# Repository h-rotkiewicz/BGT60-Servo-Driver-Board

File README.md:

# BGT60 Servo Driver Board

A USB-C powered control board built around an STM32U5 microcontroller, featuring a FFC connector interface to a BGT60TR13C radar daughterboard for non-contact sensing, and six independent DC motor/servo outputs for actuation.

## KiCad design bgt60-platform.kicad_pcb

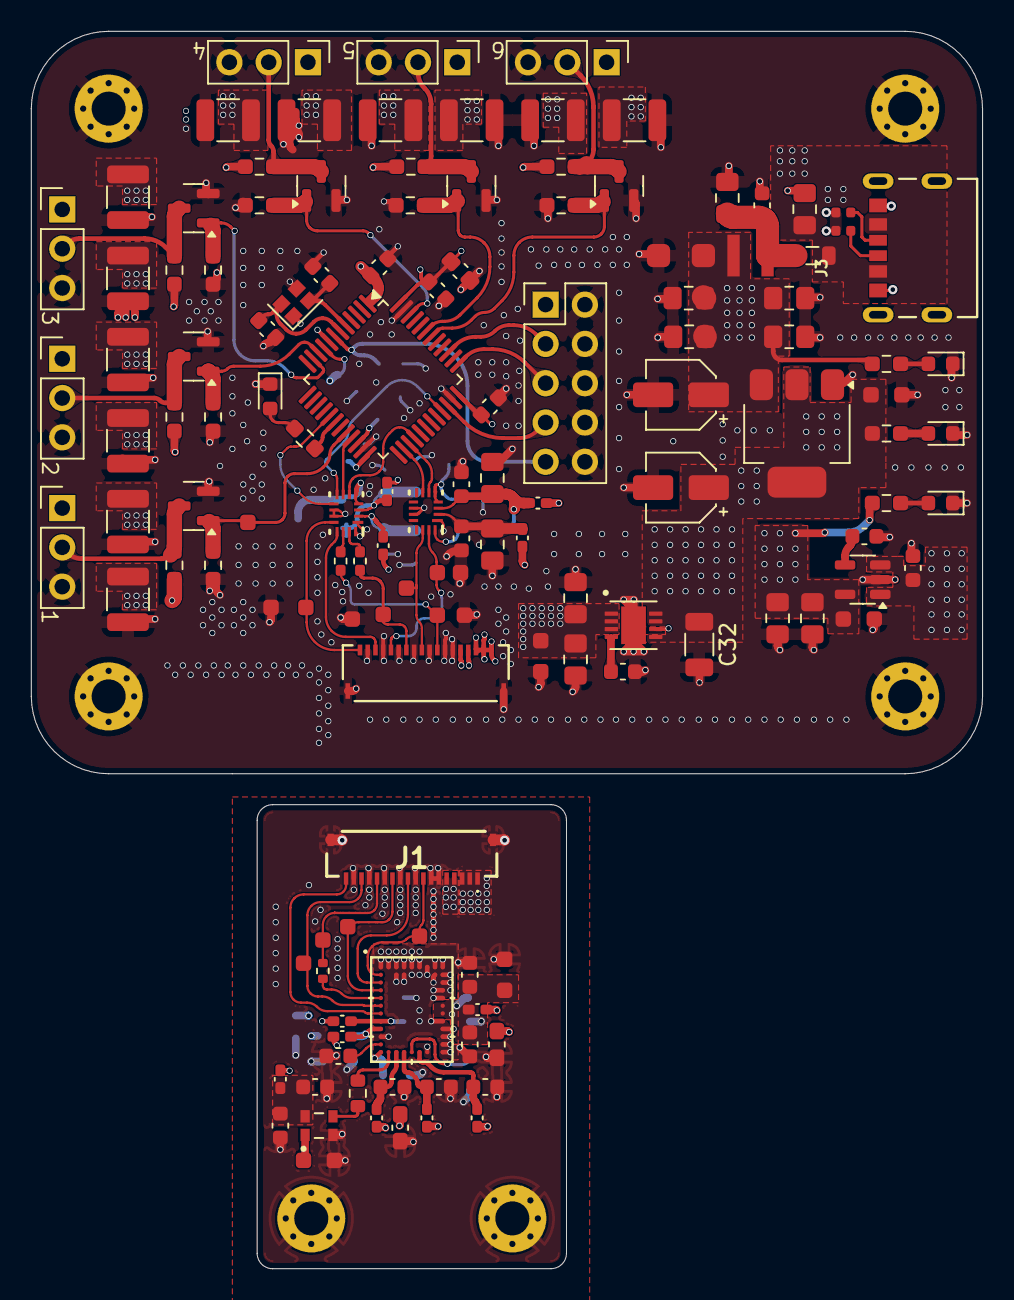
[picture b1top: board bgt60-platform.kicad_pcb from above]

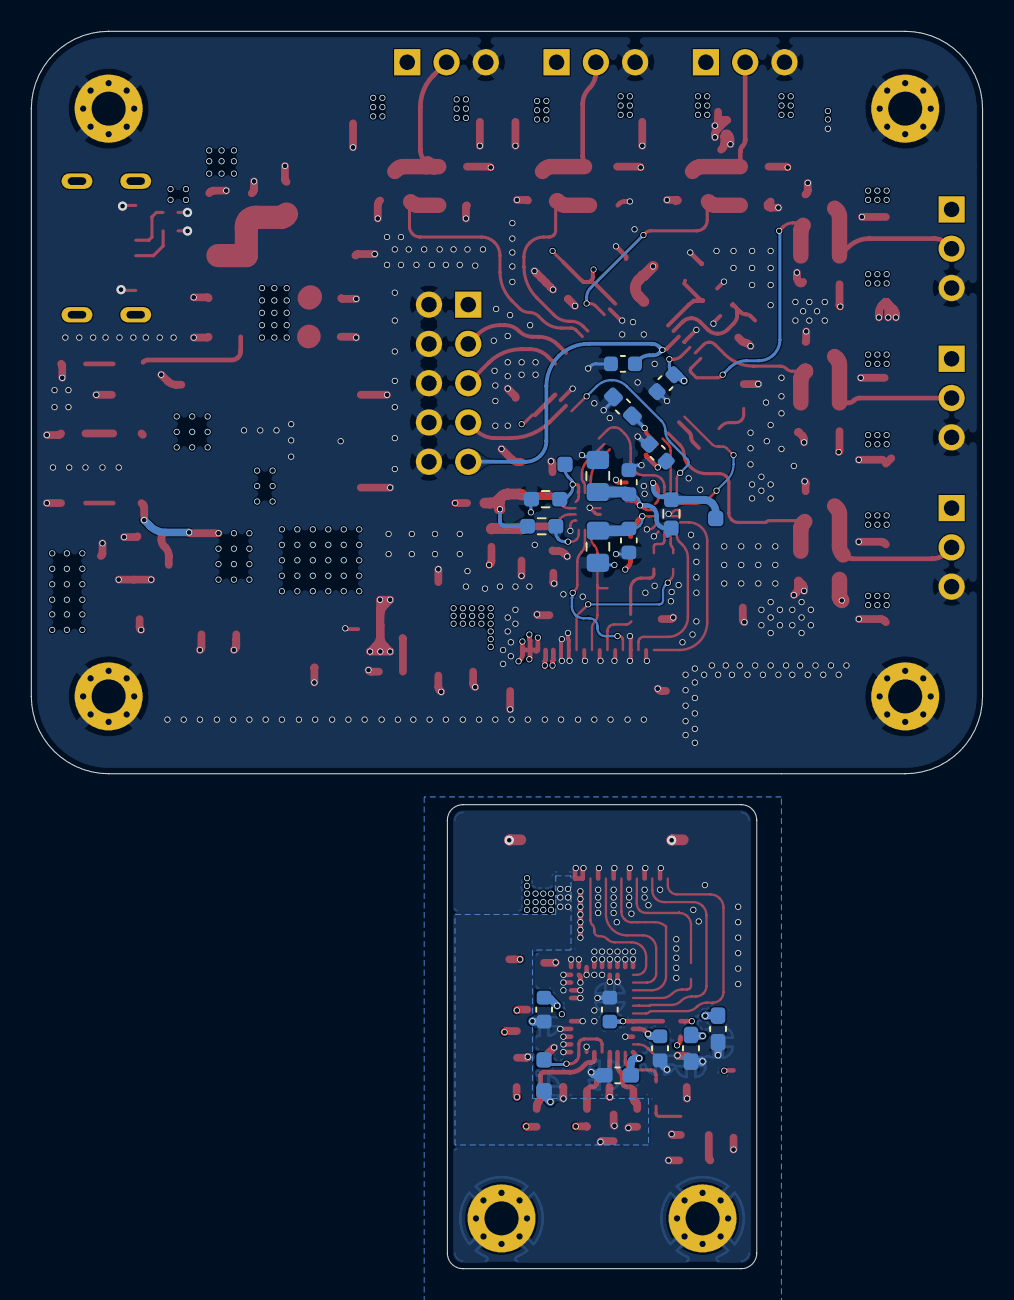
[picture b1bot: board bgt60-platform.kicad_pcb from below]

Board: 4 copper layers, 61.5 x 80.0 mm, 157 parts (20 on the bottom side), 76 nets.

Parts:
C1, C5, C7, C21, C22, C23, C24, C25, C51#2: 10u; C_0805_2012Metric_Pad1.18x1.45mm_HandSolder
C2: 100u; C_0805_2012Metric_Pad1.18x1.45mm_HandSolder
C3, C4, C6, C8, C26, C41, C42, C43, C44, C45, C46, C47, C48, C49: 1u; C_0603_1608Metric
C9, C16: 4.7u; C_0603_1608Metric_Pad1.08x0.95mm_HandSolder
C10, C14: 4p; C_0603_1608Metric
C11, C12, C13, C15, C17, C18, C20, C50: 100n; C_0603_1608Metric
C27, C29: 10u; CP_Elec_4x3
C28: 0.47n; C_0603_1608Metric
C30, C31, C34, C35: 22u; C_0805_2012Metric_Pad1.18x1.45mm_HandSolder
C32: 10u; C_1206_3216Metric
C33: 1n; C_0603_1608Metric
C36, C37, C38, C39, C40: 10u; C_0603_1608Metric_Pad1.08x0.95mm_HandSolder
C51: 470n; C_0603_1608Metric
C52, C53, C54, C55, C56, C57, C58, C59, C60, C61, C62, C63: 47u; C_1210_3225Metric
D1: LED YG; LED_0603_1608Metric
D2, D3, D4: LED GREEN; D_0603_1608Metric
FB1, FB2, FB3, FB4, FB6, FB7, FB8, FB9, FB10, FB11, FB12: 600@100M; L_0402_1005Metric_Pad0.77x0.64mm_HandSolder
FB5: 120@100M; L_0805_2012Metric
H1, H2, H3, H4: MountingHole_Pad; MountingHole_2.2mm_M2_Pad_Via
J1: 0.5K-HX-18PWB; 05KHX18PWB
J1#2: 5034801800; CON_5034801800_MOL
J2: SWD; PinHeader_2x05_P2.54mm_Vertical
J3: USB-C_CUI_UJC-HP-3-SMT-TR; USB-C_Receptacle_CUI_UJC-HP-3-SMT-TR
L1: 10u; L_1212
Q1, Q2, Q3, Q4, Q5, Q6: 2N7002BK; SOT-23
R1, R2, R3, R10, R11, R12, R16, R17, R18: 5k; R_0603_1608Metric_Pad0.98x0.95mm_HandSolder
R4, R7, R8, R9: 1k; R_0603_1608Metric_Pad0.98x0.95mm_HandSolder
R5, R6: R_5k1_0402; R_0402_1005Metric
R13, R14, R15, R19, R20, R21: 10k; R_0603_1608Metric_Pad0.98x0.95mm_HandSolder
R22: 150R; R_0603_1608Metric
R27, R28: 22; R_0402_1005Metric_Pad0.72x0.64mm_HandSolder
R29: 22; R_0402_1005Metric
Servo_1, Servo_2, Servo_3, Servo_4, Servo_5, Servo_6: Conn_01x03; PinHeader_1x03_P2.54mm_Vertical
TP1, TP1#2, TP2, TP2#2, TP3, TP3#2, TP4, TP4#2, TP5, TP6, TP7, TP8, TP9, TP14, TP17#2, TP18: TestPoint
TP10, TP11, TP12, TP13, TP15, TP16, TP17: TestPoint; Test pads 2 terminal
U1, U2: SN74AVCH4T245RSVR; RSV0016A
U3: STM32U585CIT3; LQFP-48_7x7mm_P0.5mm
U4: LD1117S33TR; SOT-223-3_TabPin2
U5: MIC5207-3.3YM5-TR; SOT-23-5
U6: ADM7170ACPZ-1.8-R7; SON50P300X300X80-9N
U7: BGT60TR13CE6327XUMA1; PG-VF2BGA-40-1
Y1: Crystal_GND23_Small; Crystal_SMD_2016-4Pin_2.0x1.6mm
Y2: KC2016Z80.0000C15XXK; OSC_KC2016Z80.0000C15XXK-4

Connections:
1.8VDR: C36.1, C38.1, C39.1, FB6.1, FB8.1, FB9.1, FB10.1, FB11.1, FB12.2, J1.1, J1.2, J1.3
1.8VDR_BB: C34.1, C35.1, FB1.1, FB3.1, J1#2.16, J1#2.17, J1#2.18, TP13.1, U6.1 (VOUT), U6.2 (VOUT__1), U6.3 (SENSE)
5V: C22.1, C23.1, C24.1, C25.1, C26.1, C27.1, L1.2, R7.1, R10.2, R11.2, R12.2, R16.2, R17.2, R18.2, TP10.1, U4.3 (VI), U5.1 (IN), U5.3 (EN)
+3V3: C9.1, C11.1, C13.1, C15.1, C17.1, C18.1, C29.1, C32.1, FB2.1, FB4.2, J2.1, R8.1, TP12.1, U3.1 (VBAT), U3.9 (VDDA), U3.24 (VDD), U3.36 (VDD), U3.48 (VDD), U4.2 (VO), U6.5 (EN), U6.7 (VIN), U6.8 (VIN__1)
+3V3R: C37.1, FB7.1, J1.4, J1.5
+3V3R_BB: C30.1, C31.1, J1#2.14, J1#2.15, R9.1, TP11.1, U5.5 (OUT)
/BGT_IRQ: J1.10, U1.7 (1A2), U3.26 (PB13), U7.C1 (IRQ)
/BGT_IRQ1.8V: J1#2.9, TP5.1 (1_1), U1.14 (1B2)
/BGT_RST: J1.16, TP4.1, U7.F1 (DIO3)
/BGT_RST1.8V: J1#2.3, U2.13 (2B1)
/BGT_reset: U2.8 (2A1), U3.33 (PA12)
/NRST: C12.1, J2.9, U3.7 (NRST)
/OSC_80M: R22.2, U7.M2 (OSC_CLK)
/PH0: C10.1, U3.5 (PH0), Y1.2
/PH1: C14.1, U3.6 (PH1), Y1.4
/PWM1: Q1.3 (D), R10.1, Servo_1.2
/PWM2: Q2.3 (D), R11.1, Servo_2.2
/PWM3: Q3.3 (D), R12.1, Servo_3.2
/PWM4: Q4.3 (D), R16.1, Servo_4.2
/PWM5: Q5.3 (D), R17.1, Servo_5.2
/PWM6: Q6.3 (D), R18.1, Servo_6.2
/PWM_GEN1: Q1.1 (G), R13.2, TP14.1 (1_1), U3.20 (PB2)
/PWM_GEN2: Q2.1 (G), R14.2, U3.46 (PB9)
/PWM_GEN3: Q3.1 (G), R15.2, U3.43 (PB7)
/PWM_GEN4: Q4.1 (G), R19.2, U3.42 (PB6)
/PWM_GEN5: Q5.1 (G), R20.2, U3.10 (PA0)
/PWM_GEN6: Q6.1 (G), R21.2, U3.11 (PA1)
/SPI2_MISO: U1.6 (1A1), U3.27 (PB14)
/SPI2_MOSI: U2.6 (1A1), U3.28 (PB15)
/SPI2_NSS: U2.9 (2A2), U3.17 (PA7)
/SPI2_SCK: U2.7 (1A2), U3.21 (PB10)
/SPI_CLK: J1.8, TP3.1, U7.B1 (CLK)
/SPI_CLK1.8V: J1#2.11, R28.1, TP2#2.1 (1_1)
/SPI_MISO: J1.14, R29.1, TP1.1
/SPI_MISO1.8V: J1#2.5, TP4#2.1 (1_1), U1.15 (1B1)
/SPI_MOSI: J1.12, TP2.1, U7.D1 (DI)
/SPI_MOSI1.8V: J1#2.7, R27.1, TP3#2.1 (1_1)
/SWCLK: J2.5, U3.37 (PA14)
/SWDIO: J2.7, U3.34 (PA13)
/SWO: J2.3, U3.39 (PB3)
/VCCA: C1.1, C3.1, FB2.2, R3.1, U2.3 (VCCA)
/VCCB: C2.1, C4.1, FB1.2, U2.2 (VCCB)
/VDDA: C43.1, FB9.2, U7.J1 (VDDA)
/VDDD: C42.1, FB8.2, U7.H1 (VDDD)
/VDDLF: C41.1, FB7.2, U7.M3 (VDDLF)
/VDDPLL: C47.1, FB10.2, U7.M4 (VDDPLL)
/VDDRF: C40.1, C44.1, C45.1, C46.1, FB6.2, TP17.1, U7.F9 (VDDRF), U7.G9 (VDDRF), U7.M1 (VDDRF)
/VDDVCO: C48.1, FB11.2, U7.M6 (VDDVCO)
/~SPI_CS: J1.18, U7.G1 (CS_N)
/~SPI_CS1.8V: J1#2.1, TP1#2.1 (1_1), U2.12 (2B2)
GND: C1.2, C2.2, C3.2, C4.2, C5.2, C6.2, C7.2, C8.2, C9.2, C10.2, C11.2, C12.2, C13.2, C14.2, C15.2, C16.2, C17.2, C18.2, C20.2, C21.2, C22.2, C23.2, C24.2, C25.2, C26.2, C27.2, C28.2, C29.2, C30.2, C31.2, C32.2, C33.2, C34.2, C35.2, C36.2, C37.2, C38.2, C39.2, C40.2, C41.2, C42.2, C43.2, C44.2, C45.2, C46.2, C47.2, C48.2, C49.2, C50.2, C51.2, C51#2.2, C52.2, C53.2, C54.2, C55.2, C56.2, C57.2, C58.2, C59.2, C60.2, C61.2, C62.2, C63.2, D1.1 (K), D2.1 (K), D3.1 (K), D4.1 (K), H1.1 (1_1), H2.1 (1_1), H3.1 (1_1), H4.1 (1_1), J1.6, J1.7, J1.9, J1.11, J1.13, J1.15, J1.17, J1.MP1, J1.MP2, J1#2.2, J1#2.4, J1#2.6, J1#2.8, J1#2.10, J1#2.12, J1#2.13, J1#2.P1, J1#2.P2, J2.2, J2.4, J2.6, J2.8, J2.10, J3.A12 (GND), J3.B12 (GND), Q1.2 (S), Q2.2 (S), Q3.2 (S), Q4.2 (S), Q5.2 (S), Q6.2 (S), R2.2, R5.1, R6.1, R13.1, R14.1, R15.1, R19.1, R20.1, R21.1, Servo_1.3, Servo_2.3, Servo_3.3, Servo_4.3, Servo_5.3, Servo_6.3, TP6.1 (1_1), TP7.1 (1_1), TP10.2, TP11.2, TP12.2, TP13.2, TP15.2, TP16.2, TP17.2, TP17#2.1 (1_1), TP18.1 (1_1), U1.1 (1OE_N), U1.10 (GND), U1.11 (GND), U2.1 (1OE_N), U2.10 (GND), U2.11 (GND), U2.16 (2OE_N), U3.8 (VSSA), U3.23 (VSS), U3.35 (VSS), U3.47 (VSS), U4.1 (GND), U5.2 (GND), U6.6 (GND), U6.9 (EXP), U7.A1 (VSSD), U7.A2 (VSSD), U7.A3 (VSSRF), U7.A4 (VSSRF), U7.A5 (VSSRF), U7.A6 (VSSRF), U7.A7 (VSSRF), U7.A8 (VSSRF), U7.A9 (VSSRF), U7.B3 (VSSRF), U7.B4 (VSSRF), U7.B8 (VSSRF), U7.B9 (VSSRF), U7.C9 (VSSRF), U7.D9 (VSSRF), U7.E9 (VSSRF), U7.H9 (VSSRF), U7.J9 (VSSRF), U7.K1 (VSSA), U7.K9 (VSSRF), U7.L9 (VSSRF), U7.M7 (VSSRF), U7.M9 (VSSRF), Y1.1, Y1.3, Y2.2 (CASE_GND)
unnamed: C20.1, C21.1, FB5.2, L1.1
unnamed: D1.2 (A), R4.2
unnamed: D2.2 (A), R7.2
unnamed: D3.2 (A), R8.2
unnamed: D4.2 (A), R9.2
unnamed: J3.A5 (CC_{1}), R6.2
unnamed: J3.B5 (CC_{2}), R5.2
unnamed: R2.1, TP8.1 (1_1), U1.4 (1DIR), U1.5 (2DIR)
unnamed: R1.1, U1.16 (2OE_N)
unnamed: C7.1, C8.1, FB4.1, R1.2, U1.3 (VCCA)
unnamed: C5.1, C6.1, FB3.2, U1.2 (VCCB)
unnamed: R27.2, U2.15 (1B1)
unnamed: R28.2, U2.14 (1B2)
unnamed: R3.2, TP9.1 (1_1), U2.4 (1DIR), U2.5 (2DIR)
unnamed: R4.1, U3.18 (PB0)
unnamed: C16.1, U3.22 (VCAP)
unnamed: C28.1, U5.4 (BP)
unnamed: C33.1, U6.4 (SS)
unnamed: TP16.1, U7.M5 (DIV_TEST)
unnamed: R29.2, U7.E1 (DO)
unnamed: C51.1, U7.L1 (VAREF)
unnamed: TP15.1, Y2.1 (INH)
unnamed: R22.1, Y2.3 (OUTPUT)
unnamed: C49.1, C50.1, FB12.1, Y2.4 (VCC)
VBUS: C51#2.1, C52.1, C53.1, C54.1, C55.1, C56.1, C57.1, C58.1, C59.1, C60.1, C61.1, C62.1, C63.1, FB5.1, J3.A9 (VBUS), J3.B9 (VBUS), Servo_1.1, Servo_2.1, Servo_3.1, Servo_4.1, Servo_5.1, Servo_6.1

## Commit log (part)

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2025-05-20 Initial project scaffold and top-level schematic
2025-05-22 Add power supply schematic
2025-05-25 Add radar sensor interface schematic
2025-05-27 Add MOSFET switching stage for motor control
2025-06-01 Initial PCB layout: board outline, layer stackup, and component placement
2025-06-05 Configure net classes, track widths, and via dimension presets
2025-06-09 Add teardrop and tuning pattern routing settings
2025-06-13 DRC rule tuning and copper zone settings
2025-06-17 Add fabrication toolkit and round tracks configuration
2025-06-20 Add 3D model export for board visualization
2025-06-22 Add README with board description and render

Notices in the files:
parts and their libraries:
License: Apache-2.0
